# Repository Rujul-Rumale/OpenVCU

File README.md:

<div align="center">

# OpenVCU

### Open Vehicle Control Unit — one board, every vehicle.

**Quad · Plane · Rover · Boat — configurable STM32H7 controller for anything that moves.**

*Open hardware. Designed from scratch. Built to be flashed for whatever you bolt it to.*

</div>

---

## What is this?

OpenVCU is an **open-source vehicle control unit** built around the **STM32H743VIT6** (480&nbsp;MHz Cortex-M7, 2&nbsp;MB flash, 1&nbsp;MB RAM).

Off-the-shelf F4 flight controllers run out of headroom when you fuse RTK GPS + IMU at high rates for EKF-heavy work like 3D photogrammetry surveys. OpenVCU is my answer: H7-class compute, a clean sensor set, and one PCB that can be configured as a **quad, fixed-wing, rover, or boat** controller.

> ⚠️ **WIP — schematic in progress.** The schematic is done and under review; **layout hasn't started** and nothing has been manufactured. Firmware lives out-of-tree for now and is intentionally **not in this repo**.

---

## One board, four vehicles

| Vehicle | What OpenVCU gives you |
| :--- | :--- |
| 🚁 **Quad** | 4× PWM motor outputs (TIM1), 6-axis IMU + baro, SD logging |
| ✈️ **Plane** | PWM for elevon / tail / throttle + UART GPS + I2C compass header |
| 🚗 **Rover** | PWM for steering + throttle, battery sensing, FRAM for params |
| 🚤 **Boat** | Same as rover + sealed-box-friendly USB-C + SD blackbox |

All vehicle personalities share the same core: **IMU → EKF → PWM + telemetry + log**. The difference is just configuration and wiring.

---

## Hardware at a glance

| Block | Part | Notes |
| :--- | :--- | :--- |
| MCU | **STM32H743VIT6** | 480&nbsp;MHz M7, LQFP-100, 8&nbsp;MHz HSE + 32.768&nbsp;kHz LSE |
| IMU | **ICM-42688-P** | 6-axis, SPI, 32&nbsp;kHz ODR |
| Baro | **DPS310** | I2C `0x76`, interrupt pin routed |
| Logging | **FM25V02A** FRAM 256&nbsp;KB (SPI) + **microSD** over SDMMC1 4-bit | Params + blackbox |
| Power | LiPo → **MP1584EN** buck (5&nbsp;V) → **AP2112K** 3.3&nbsp;V LDO | Fused + reverse-protected input |
| USB | **USB-C** + USBLC6-2SC6 ESD | 5.1&nbsp;kΩ CC pull-downs |
| Compass | External via I2C header | For real heading on rovers / boats / planes |

---

## Interfaces

### PWM motor / servo outputs

| Output | MCU pin | Timer |
| :--- | :--- | :--- |
| OUT 1 | PE9 | TIM1_CH1 |
| OUT 2 | PE11 | TIM1_CH2 |
| OUT 3 | PE13 | TIM1_CH3 |
| OUT 4 | PE14 | TIM1_CH4 |

Quads take all four. Planes / rovers / boats just remap them (e.g. steering + throttle).

### Comms & storage

| Bus | Use |
| :--- | :--- |
| UART1 / UART3 / UART6 | GPS, telemetry radio, RC |
| I2C1 / I2C2 | Onboard DPS310 + external compass |
| SPI1 | ICM-42688-P |
| SPI2 / SPI3 | Expansion + FM25V02A FRAM |
| SDMMC1 | microSD 4-bit |
| USB OTG_FS | USB-C (PA11/PA12) |

### SWD debug header

| Pin | Signal |
| :--- | :--- |
| 1 | +3V3 |
| 2 | SWDIO (PA13) |
| 3 | SWCLK (PA14) |
| 4 | GND |

Flash with ST-Link + STM32CubeProgrammer once firmware lands.

---

## Repo structure

```
OpenVCU/
├── PCB/          # KiCad 10 — schematics + project libs (layout stays local)
│   ├── OpenVCU.kicad_sch      # root sheet
│   ├── Power.kicad_sch
│   ├── Sensors.kicad_sch
│   ├── Peripherals.kicad_sch
│   ├── OpenVCU.kicad_sym      # project symbols
│   └── OpenVCU.pretty/        # project footprints
├── bom/          # BOM CSV + interactive BOM
├── docs/
│   └── datasheets/            # vendor datasheets for every key part
├── LICENSE          # CERN-OHL-S-2.0 — hardware (PCB/, bom/)
├── LICENSE-MIT      # MIT — docs/, everything else
├── CONTRIBUTING.md
└── README.md
```

> Only schematics + libraries live in git. Layout (`.kicad_pcb`), gerbers, and firmware are **deliberately excluded** for now — layout is still WIP, firmware lands as `Firmware/` once the board is validated.

---

## Status & roadmap

- ✅ Schematic complete (hierarchical: Power / Sensors / Peripherals)
- ✅ BOM + interactive BOM exported
- 🚧 **Layout in progress** — not in git yet, no gerbers, nothing ordered
- ⏳ **Finish layout → DRC → manufacture rev A**
- ⏳ Bring-up: power rails → SWD → IMU/baro probe → SD + FRAM
- ⏳ Firmware bring-up (out-of-tree until hardware is proven)
- ⏳ Vehicle configs: quad → plane → rover → boat

---

## Getting started

### 1. Open the hardware

```bash
git clone https://github.com/<you>/OpenVCU.git
cd OpenVCU
# open PCB/OpenVCU.kicad_pro in KiCad 10
```

You need **KiCad 10** (project symbols live in `OpenVCU.kicad_sym`, footprints in `OpenVCU.pretty/`).

### 2. Review the BOM

- `bom/bom.csv` — orderable line items
- `bom/ibom.html` — interactive BOM, open in a browser

### 3. Layout / manufacturing

Layout is still WIP and lives only locally — there are no gerbers in this repo yet. Once the layout lands, re-export gerbers from the layout before ordering.

---

## Design notes

- **VCAP1/VCAP2 need exactly 2.2&nbsp;µF ceramic** or the H7 internal LDO goes unstable.
- **USB-C CC pins need 5.1&nbsp;kΩ to GND** or chargers won't enumerate the board.
- Planned stackup: 4-layer with GND pour; crystal section gets an isolated GND island.

---

## Contributing

WIP hardware — reviews welcome, especially on power, crystal, and sensor routing. See [CONTRIBUTING.md](CONTRIBUTING.md).

---

## ⚠️ Caution

Nothing here has touched real copper yet. Double-check every pin against the schematic before you fab or flash, and expect rev-A debugging.

---

## License

- **Hardware** (`PCB/`, `bom/`) — [CERN-OHL-S-2.0](LICENSE). If you make or sell boards from this design or a modified version, share your modified design files under the same license.
- **Docs, everything else** — [MIT](LICENSE-MIT).

---

## Credits

- Designed by **Rujul**
- [KiCad](https://www.kicad.org/) for schematic design
- Datasheets in `docs/datasheets/` belong to their respective vendors

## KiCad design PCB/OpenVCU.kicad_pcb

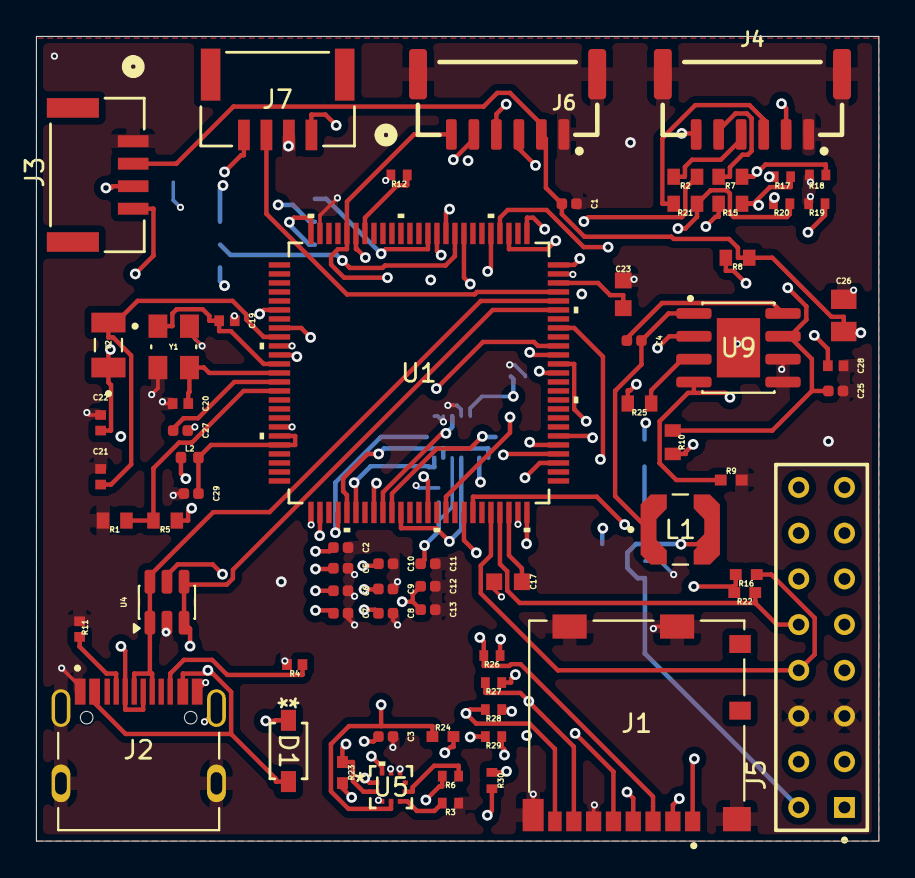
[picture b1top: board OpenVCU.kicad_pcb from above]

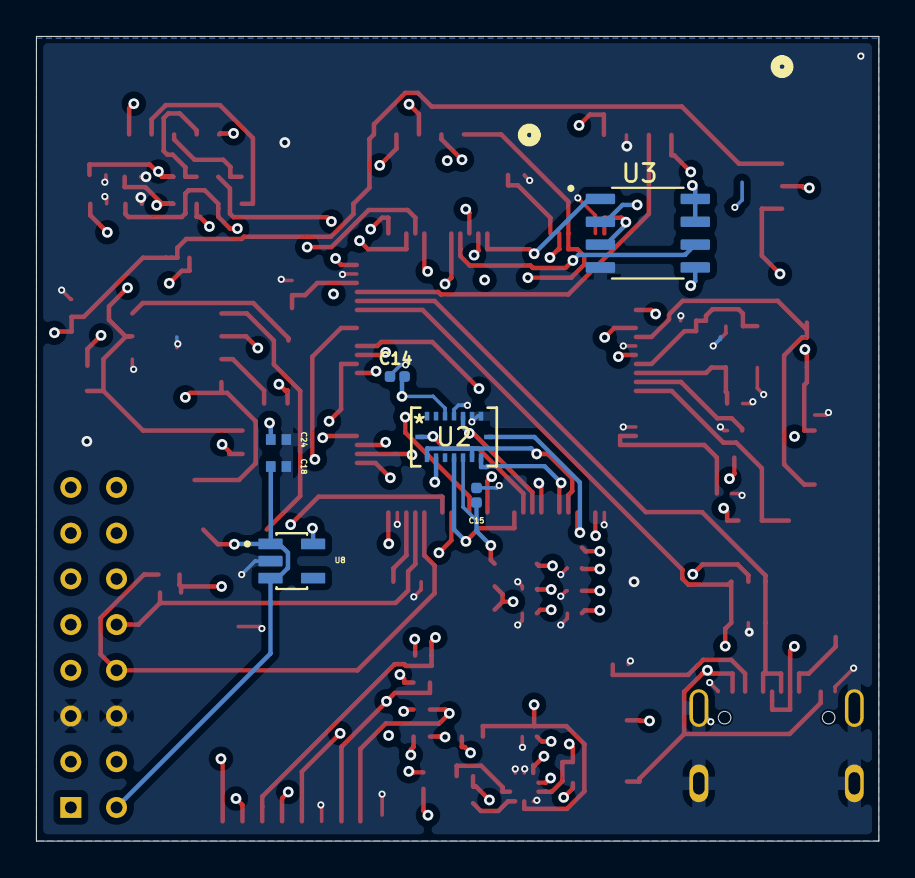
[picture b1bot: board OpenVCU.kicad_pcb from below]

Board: 4 copper layers, 46.8 x 44.7 mm, 75 parts (7 on the bottom side), 64 nets.

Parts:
C1, C2, C3, C4, C5, C6, C7, C8, C9, C10, C11, C12, C13, C14, C15, C25, C27, C29: C0402C104K3RACTU; CAPC1005X55N
C17, C23: GRM188R61C225KE15D; CAPC1608X90N
C18, C24: GRM155R61E105KA12D; CAPC1005X55N
C19, C20: GRM1555C1H180JA01D; CAPC1005X55N
C21, C22: GRM1555C1H7R0DA01D; CAPC1005X55N
C26: GRM21BR61A226ME51L; CAPC2012X140N
C28: GRM1555C1H222JA01D; CAPC1005X55N
D1: D_Schottky; SDO_SOD-123_MCC
J1: 104031-0811; MOLEX_104031-0811
J2: USB-C; HRO_TYPE-C-31-M-12
J3, J7: BM04B-GHS-TBT; CONN_BM04B-GHS-TBT_JST
J4, J6: BM06B-GHS-TBT
J5: BDL-108-X-X; SAMTEC_BDL-108-X-X
L1: LPS4018-103; IND_LPS4018-103
L2: L_Ferrite; L_0402_1005Metric
R1, R5, R8, R10, R25: RC0402FR-07100KL; RESC1005X40
R2, R7, R15, R21: RC0402FR-07100RL; RESC1005X40
R3, R6, R12, R17, R18, R19, R20, R26, R27, R28, R29, R30: RC0402FR-0710KL; RESC1005X40N
R4, R11: RC0402FR-075K1L; RESC1005X40N
R9: RC0402FR-0720KL; RESC1005X40N
R16, R22, R23, R24: RC0402FR-072K2L; RESC1005X40N
U1: STM32H743VIT6; LQFP100-14x14mm
U2: BMI088; QFN_BMI085_BOS
U3: FM25V02A-GTR; SOIC127P602X172-8N
U4: USBLC6-2SC6; SOT-23-6
U5: BMP390; 10LGA_2X2X0p75_BOS
U8: AP2112K-3.3TRG1; SOT95P285X140-5N
U9: MP1584EN; SOIC127P600X170-9N
Y1: ABM8-272-T3; XTAL_ABM8-272-T3
Y2: CM315D32768DZFT; XTAL_CM315D32768DZFT

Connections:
+3V3: C2.1, C3.1, C5.1, C6.1, C7.1, C8.1, C9.1, C10.1, C11.1, C12.1, C13.1, C14.2, C15.2, C24.1, J1.4 (VDD), J5.03, J5.04, J7.1, L2.1, R6.2, R16.2, R22.2, R23.2, R24.2, R26.1, R27.1, R28.1, R29.1, R30.1, U1.6 (VBAT), U1.11 (VDD), U1.27 (VDD), U1.50 (VDD), U1.75 (VDD), U1.100 (VDD), U2.3 (VDD), U2.11 (VDDIO), U3.3 (~WP), U3.7 (~HOLD), U3.8 (VDD), U5.1 (VDDIO), U5.10 (VDD), U8.5 (VOUT)
+5V: C1.1, C18.1, C26.1, D1.1 (K), J3.2, J5.01, J5.02, J6.2, L1.2, R8.1, U4.5 (VBUS), U8.1 (VIN), U8.3 (EN)
/BMI_INT1: U1.35 (PB1), U2.16 (INT1)
/BMI_INT3: U1.36 (PB2), U2.12 (INT3)
/Comp_resistor: R25.1, U9.3 (COMP)
/FLASH_CS: U1.87 (PD6), U3.1 (~CS)
/I2C1_SCL: J6.5, R23.1, U1.95 (PB8), U5.2 (SCK)
/I2C1_SDA: J6.6, R24.1, U1.96 (PB9), U5.4 (SDI)
/I2C2_SCL: J5.08, R16.1, U1.46 (PB10)
/I2C2_SDA: J5.10, R22.1, U1.47 (PB11)
/NRST: C27.1, U1.14 (NRST)
/PWM1: R20.1, R21.1, U1.39 (PE9)
/PWM2: R2.1, R19.1, U1.41 (PE11)
/PWM3: R7.1, R18.1, U1.43 (PE13)
/PWM4: R15.1, R17.1, U1.44 (PE14)
/SDMMC1_CLK: J1.5 (CLK), U1.80 (PC12)
/SDMMC1_CMD: J1.3 (CMD), R26.2, U1.83 (PD2)
/SDMMC1_D0: J1.7 (DAT0), R27.2, U1.65 (PC8)
/SDMMC1_D1: J1.8 (DAT1), R28.2, U1.66 (PC9)
/SDMMC1_D2: J1.1 (DAT2), R29.2, U1.78 (PC10)
/SDMMC1_D3: J1.2 (CD/DAT3), R30.2, U1.79 (PC11)
/SPI1_MISO: U1.30 (PA6), U2.10 (SDO2), U2.15 (SDO1)
/SPI1_MOSI: U1.31 (PA7), U2.9 (SDA/SDI)
/SPI1_SCK: U1.29 (PA5), U2.8 (SCL/SCK)
/SPI2_MISO: U1.85 (PD4), U3.2 (SO)
/SPI2_MOSI: U1.86 (PD5), U3.5 (SI)
/SPI2_SCK: U1.84 (PD3), U3.6 (SCK)
/SPI_CS_ACCEL: U1.33 (PC5), U2.14 (CSB1)
/SPI_CS_GYRO: U1.34 (PB0), U2.5 (CSB2)
/SWCLK: J7.4, U1.76 (PA14)
/SWDIO: J7.3, U1.72 (PA13)
/SW_NODE: C4.2, L1.1, U9.1 (SW)
/UART1_RX: J3.3, U1.54 (PB15)
/UART1_TX: J3.4, U1.53 (PB14)
/UART3_RX: J6.3, U1.56 (PD9)
/UART3_TX: J6.4, U1.55 (PD8)
/UART6_RX: J5.09, U1.64 (PC7)
/UART6_TX: J5.07, U1.63 (PC6)
/USB_D_N: J2.A7 (DN1), J2.B7 (DN2), U1.70 (PA11), U4.3 (I/O2), U4.4 (I/O2)
/USB_D_P: J2.A6 (DP1), J2.B6 (DP2), U1.71 (PA12), U4.1 (I/O1), U4.6 (I/O1)
/VBAT: C25.1, J4.2, R10.1, U9.7 (VIN)
/VBUS_DIV: R1.1, R5.2, U1.15 (PC0)
GND: C1.2, C2.2, C3.2, C5.2, C6.2, C7.2, C8.2, C9.2, C10.2, C11.2, C12.2, C13.2, C14.1, C15.1, C17.1, C18.2, C19.2, C20.1, C21.2, C22.2, C23.2, C24.2, C25.2, C26.2, C27.2, C28.2, C29.1, J1.6 (VSS), J1.G1 (GND), J1.G2 (GND), J1.G3 (GND), J1.G4 (GND), J2.A1B12 (GND), J2.B1A12 (GND), J2.S1 (SHIELD), J2.S2 (SHIELD), J2.S3 (SHIELD), J2.S4 (SHIELD), J3.1, J4.1, J4.13 (CHASSIS@1), J4.14 (CHASSIS@2), J5.05, J5.06, J6.1, J6.13 (CHASSIS@1), J6.14 (CHASSIS@2), J7.2, R1.2, R3.1, R4.2, R9.2, R11.1, R12.2, R17.2, R18.2, R19.2, R20.2, U1.10 (VSS), U1.19 (VSSA), U1.26 (VSS), U1.49 (VSS), U1.74 (VSS), U1.99 (VSS), U2.4 (GNDA), U2.6 (GNDIO), U2.7 (PS), U3.4 (VSS), U4.2 (GND), U5.3 (VSS), U5.8 (VSS), U5.9 (VSS), U8.2 (GND), U9.5 (GND), U9.6 (FREQ), U9.9 (GND), Y1.2 (GND), Y1.4 (GND)
unnamed: C28.1, R25.2
unnamed: J2.A5 (CC1), R11.2
unnamed: J2.B5 (CC2), R4.1
unnamed: J4.3, R21.2
unnamed: J4.4, R2.2
unnamed: J4.5, R7.2
unnamed: J4.6, R15.2
unnamed: R12.1, U1.94 (BOOT0)
unnamed: C22.1, U1.8 (PC14-OSC32_IN), Y2.1
unnamed: C21.1, U1.9 (PC15-OSC32_OUT), Y2.2
unnamed: C19.1, U1.12 (PH0-OSC_IN), Y1.1
unnamed: C20.2, U1.13 (PH1-OSC_OUT), Y1.3
unnamed: C17.2, U1.48 (VCAP1)
unnamed: C23.1, U1.73 (VCAP2)
unnamed: C29.2, L2.2, U1.20 (VREF+), U1.21 (VDDA)
unnamed: R6.1, U5.6 (CSB)
unnamed: R3.2, U5.5 (SDO)
unnamed: C4.1, U9.8 (BST)
unnamed: R10.2, U9.2 (EN)
unnamed: R8.2, R9.1, U9.4 (FB)
VBUS: D1.2 (A), J2.A4B9 (VBUS), J2.B4A9 (VBUS), R5.1, U1.68 (PA9)

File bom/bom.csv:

"","References","Value","Footprint","Quantity"
1,"C1, C2, C3, C4, C5, C6, C7, C8, C9, C10, C11, C12, C13, C14, C15, C25, C27, C29","C0402C104K3RACTU","CAPC1005X55N",18
2,"C17, C23","GRM188R61C225KE15D","CAPC1608X90N",2
3,"C18, C24","GRM155R61E105KA12D","CAPC1005X55N",2
4,"C19, C20","GRM1555C1H180JA01D","CAPC1005X55N",2
5,"C21, C22","GRM1555C1H7R0DA01D","CAPC1005X55N",2
6,"C26","GRM21BR61A226ME51L","CAPC2012X140N",1
7,"C28","GRM1555C1H222JA01D","CAPC1005X55N",1
8,"R3, R6, R12, R17, R18, R19, R20, R26, R27, R28, R29, R30","RC0402FR-0710KL","RESC1005X40N",12
9,"R1, R5, R8, R10, R25","RC0402FR-07100KL","RESC1005X40",5
10,"R2, R7, R15, R21","RC0402FR-07100RL","RESC1005X40",4
11,"R16, R22, R23, R24","RC0402FR-072K2L","RESC1005X40N",4
12,"R4, R11","RC0402FR-075K1L","RESC1005X40N",2
13,"R9","RC0402FR-0720KL","RESC1005X40N",1
14,"L1","LPS4018-103","IND_LPS4018-103",1
15,"L2","L_Ferrite","L_0402_1005Metric",1
16,"D1","D_Schottky","SDO_SOD-123_MCC",1
17,"U1","STM32H743VIT6","LQFP100-14x14mm",1
18,"U2","BMI088","QFN_BMI085_BOS",1
19,"U3","FM25V02A-GTR","SOIC127P602X172-8N",1
20,"U4","USBLC6-2SC6","SOT-23-6",1
21,"U5","BMP390","10LGA_2X2X0p75_BOS",1
22,"U8","AP2112K-3.3TRG1","SOT95P285X140-5N",1
23,"U9","MP1584EN","SOIC127P600X170-9N",1
24,"Y1","ABM8-272-T3","XTAL_ABM8-272-T3",1
25,"Y2","CM315D32768DZFT","XTAL_CM315D32768DZFT",1
26,"J3, J7","BM04B-GHS-TBT","CONN_BM04B-GHS-TBT_JST",2
27,"J4, J6","BM06B-GHS-TBT","BM06B-GHS-TBT",2
28,"J1","104031-0811","MOLEX_104031-0811",1
29,"J2","USB-C","HRO_TYPE-C-31-M-12",1
30,"J5","BDL-108-X-X","SAMTEC_BDL-108-X-X",1

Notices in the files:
parts and their libraries:
COPYRIGHT: Copyright (C) 2023 Ultra Librarian. All rights reserved.
